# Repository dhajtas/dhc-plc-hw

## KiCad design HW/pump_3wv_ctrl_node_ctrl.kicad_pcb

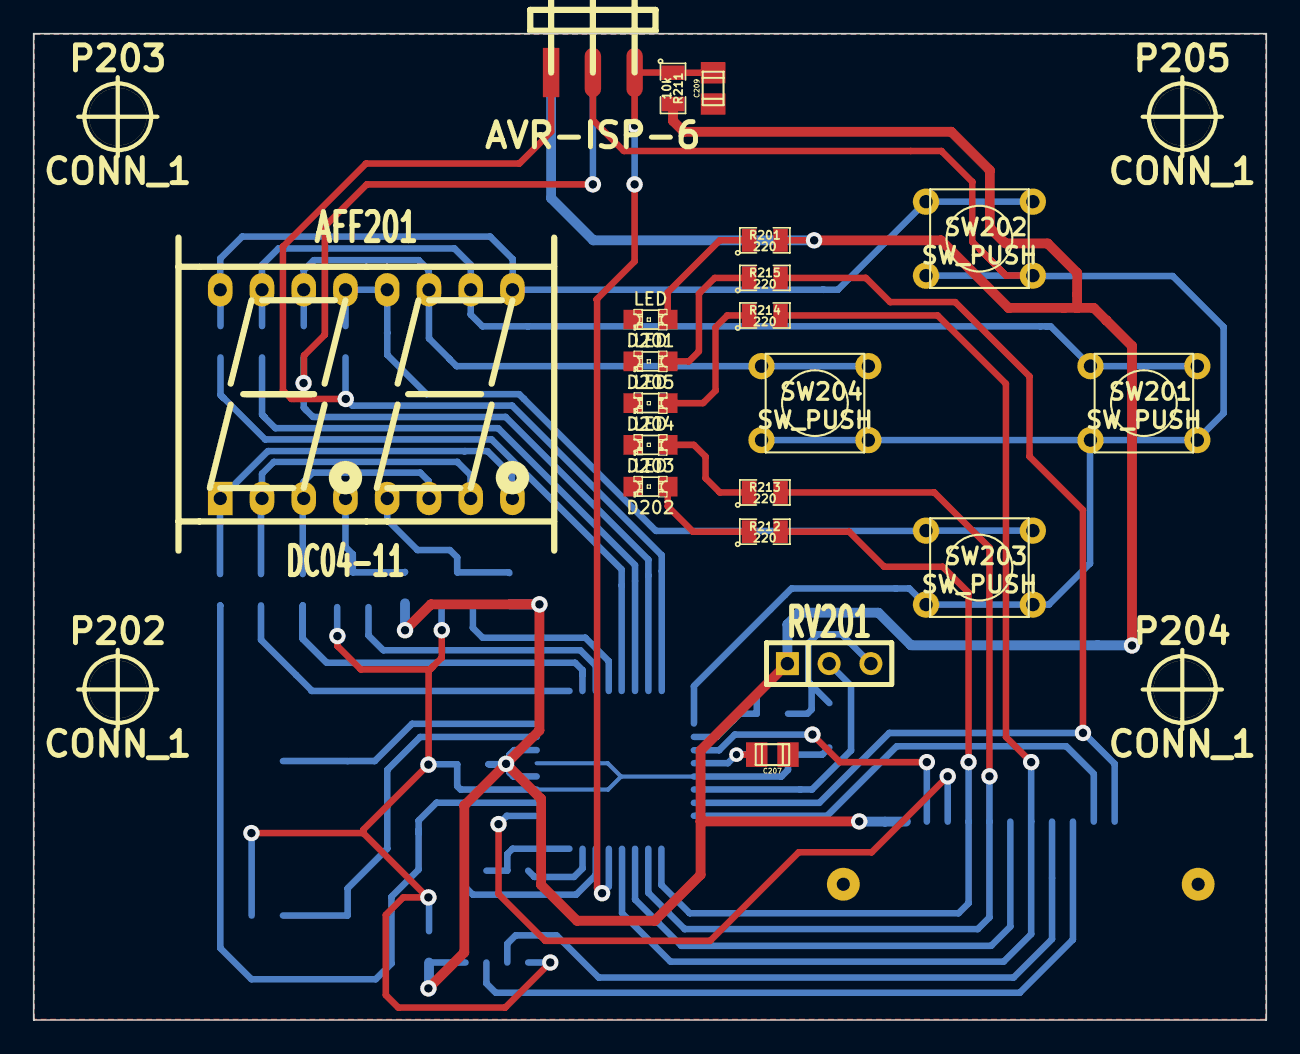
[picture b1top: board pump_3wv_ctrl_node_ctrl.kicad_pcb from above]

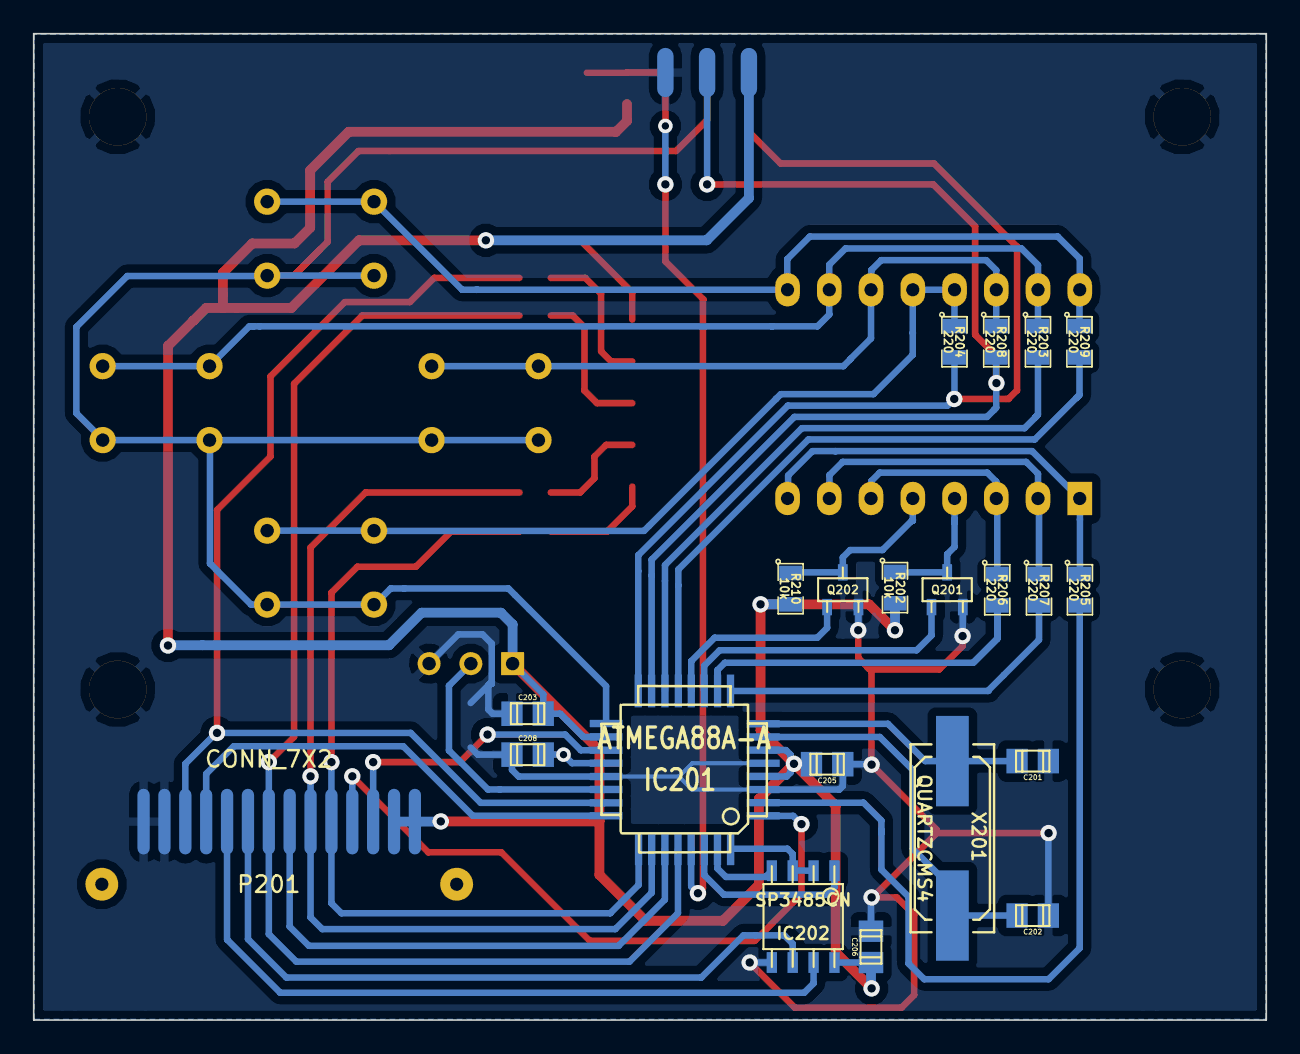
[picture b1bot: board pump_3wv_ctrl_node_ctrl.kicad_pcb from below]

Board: 2 copper layers, 75.0 x 60.0 mm, 45 parts (21 on the bottom side), 44 nets.

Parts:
AFF201: DC04-11; Dx04
C201, C202: 12p; c_0805
C203, C205, C206, C208: 100n; c_0805
C207, C209: 1u; c_0805
CON201: AVR-ISP-6; avr_isp_6_edge
D201, D202, D203, D204, D205: LED; LED-0805
IC201: ATMEGA88A-A; TQFP32
IC202: SP3485CN; so-8
P201: CONN_7X2; 14pin_flatcable_pcbstrip
P202, P203, P204, P205: CONN_1; hole_3mm5
Q201, Q202: MOS_N_DHA; sot23
R201, R203, R204, R205, R206, R207, R208, R209, R212, R213, R214, R215: 220; SM0805
R202, R210, R211: 10k; SM0805
RV201: POT; SIL-3
SW201, SW202, SW203, SW204: SW_PUSH; SW_KSM61x
X201: QUARTZCMS4; Q_49U3HMS

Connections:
+5V: C203.1, C205.1, C206.2, CON201.2, IC201.4, IC201.6, IC201.18, IC202.8, P201.1, P201.2, R201.2, R202.2, R210.2, R211.2, RV201.1
/485_A: IC202.6, P201.9
/485_B: IC202.7, P201.10
/A: AFF201.10, AFF201.15, R203.1, SW201.1
/AA: IC201.14, R203.2
/B: AFF201.12, AFF201.13, R204.1, SW203.1
/C: AFF201.1, AFF201.8, R205.1
/CC: IC201.2, R205.2
/D: AFF201.3, AFF201.6, R206.1
/D1: AFF201.4, Q201.2, R202.1
/D2: AFF201.5, Q202.2, R210.1
/DD: IC201.10, R206.2
/E: AFF201.2, AFF201.7, R207.1
/EE: IC201.9, R207.2
/F: AFF201.11, AFF201.14, R208.1, SW204.1
/G: AFF201.9, AFF201.16, R209.1, SW202.1
/G1: IC201.11, Q201.1
/G2: IC201.12, Q202.1
/GG: IC201.13, R209.2
/IN: IC201.19, P201.3
/MISO: CON201.1, IC201.16, R204.2
/MOSI: CON201.4, IC201.15, R208.2
/PULSE1: IC201.28, P201.8, R214.2
/PULSE2: IC201.26, P201.6, R213.2
/PULSE3: IC201.25, P201.5, R212.2
/SCK: CON201.3, IC201.17, SW201.2, SW202.2, SW203.2, SW204.2
/SWFB: IC201.24, P201.11
/SWITCH: IC201.23, P201.12, R215.2
/W1: IC201.27, P201.7
/ZCD: IC201.1, P201.4
/ref: C207.1, C208.1, IC201.20
/reset: C209.1, CON201.5, IC201.29, R211.1
/xtal1: C202.1, IC201.7, X201.2
/xtal2: C201.1, IC201.8, X201.1
GND: C201.2, C202.2, C203.2, C205.2, C206.1, C207.2, C208.2, C209.2, CON201.6, D201.2, D202.2, D203.2, D204.2, D205.2, IC201.3, IC201.5, IC201.21, IC202.5, P201.13, P201.14, P202.1, P203.1, P204.1, P205.1, Q201.3, Q202.3, RV201.3
unnamed: D205.1, R215.1
unnamed: D202.1, R212.1
unnamed: D203.1, R213.1
unnamed: D204.1, R214.1
unnamed: IC201.32, IC202.2, IC202.3
unnamed: IC201.30, IC202.1
unnamed: D201.1, R201.1
unnamed: IC201.22, RV201.2
unnamed: IC201.31, IC202.4

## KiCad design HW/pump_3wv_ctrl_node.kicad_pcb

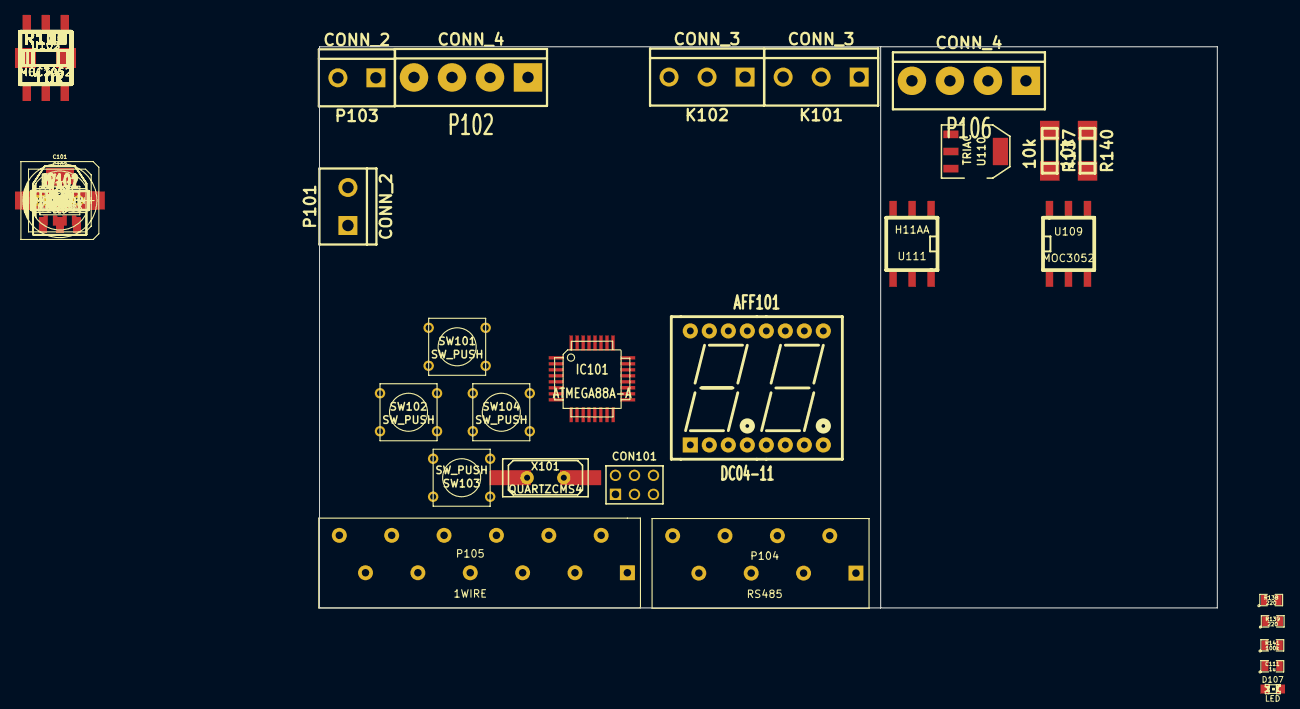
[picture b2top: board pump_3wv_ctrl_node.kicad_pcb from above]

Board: 2 copper layers, 120.0 x 75.0 mm, 94 parts (0 on the bottom side), 75 nets, no tracks yet.

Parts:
AFF101: DC04-11; Dx04
C101: 100u/63V; c_elec_10x10
C102: 470u/10V; c_elec_8x10
C103: 470p; SM0805
C104, C105: 12p; SM0805
C106, C107, C108, C110, C121: 100n; SM0805
C109: 1u; SM1206
C111: 1u; SM0805
C122: 10p; SM0805
CON101: AVR-ISP-6; pin_array_3x2
D101: transil 38V; SM2010
D102: SK110; SM0805
D103, D104, D105, D106, D107: LED; LED-0805
FB101: FILTER; SM0805
IC101: ATMEGA88A-A; TQFP32
JP101: JUMPER3; SIL-3
JP102: JUMPER; SIL-2
K101, K102: CONN_3; bornier3
P101, P103: CONN_2; bornier2
P102, P106: CONN_4; bornier4
P104: RS485; wago_250-208
P105: 1WIRE; wago_250-212
Q101, Q102: MOS_N_DHA; SOT23GDS
R101, R102, R104: 1; SM0805
R103: 100; SM0805
R105: 3k6; SM0805
R106: 1k2; SM0805
R107, R121, R133, R135, R136: 10k; SM0805
R108, R109, R110, R111, R113, R116, R117, R120, R122, R125, R137, R140: 10k; MELF0207
R112, R114, R115, R118, R119, R123, R124, R126, R127, R128, R129, R130, R131, R132, R138, R139: 220; SM0805
R134: 120; SM0805
R141: 100k; SM0805
RV101: POT; SIL-3
SW101, SW102, SW103, SW104: SW_PUSH; SW_PUSH_SMALL
U101: MC34063; SO8E
U102, U111: H11AA; SMD_DIL6
U103, U105, U107, U109: MOC3052; SMD_DIL6
U104, U106, U108, U110: TRIAC; SOT223
X101: QUARTZCMS4; Q_49_SMD_TH

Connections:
+5V: C102.1, C106.1, C107.1, C108.1, C121.2, CON101.2, IC101.4, IC101.6, IC101.18, JP101.1, P105.3, P105.6, P105.9, P105.12, R105.2, R107.1, R112.2, R121.2, R133.2, R135.2, R136.2, RV101.1
+24V: D101.2, JP101.3, P101.1, R103.1
/A: AFF101.10, AFF101.15, JP102.2, P104.3, P104.7, R126.1, SW101.1
/B: AFF101.12, AFF101.13, P104.2, P104.6, R127.1, R134.1, SW102.1
/C: AFF101.1, AFF101.8, R128.1, SW103.1
/D: AFF101.3, AFF101.6, R129.1, SW104.1
/D1: AFF101.4, R135.1
/D2: AFF101.5, R136.1
/E: AFF101.2, AFF101.7, R130.1
/F: AFF101.11, AFF101.14, R131.1
/G: AFF101.9, AFF101.16, R132.1
/G3: IC101.26, SW101.2, SW102.2, SW103.2, SW104.2
/IN: IC101.19, P103.1, R133.1
/L: K101.3, P106.2, R111.1, R113.1, R117.1, R122.1, U104.2, U106.2, U108.2
/L1: K102.3, U108.1
/L2: P102.4, U106.1
/L3: P102.3, U104.1
/N: K101.1, K102.1, P102.1, P106.1, R109.1, U111.1
/PULSE1: IC101.2, R123.2, R124.2
/PULSE2: IC101.9, R118.2, R119.2
/PULSE3: IC101.10, R114.2, R115.2
/PWR1: FB101.1, R103.2
/PWR2: C101.1, FB101.2, R101.1, R102.1, R104.1, U101.6
/PWR3: R101.2, R102.2, R104.2, U101.1, U101.7, U101.8
/PWR4: D102.2, U101.2
/SWFB: C111.1, IC101.27, R141.2, U111.5
/SWITCH: IC101.28, R138.2, R139.2
/W1: IC101.11, P105.2, P105.5, P105.8, P105.11
/ZCD: IC101.1, R107.2, U102.5
/ref: C109.1, C110.1, IC101.20
/reset: C122.1, CON101.5, IC101.29, R121.1
/xtal1: C105.1, IC101.7
/xtal2: C104.1, IC101.8, X101.1
GND: C101.2, C102.2, C103.2, C104.2, C105.2, C106.2, C107.2, C108.2, C109.2, C110.2, C111.2, C121.1, C122.2, CON101.6, D101.1, D102.1, D103.2, D104.2, D105.2, D106.2, D107.2, IC101.3, IC101.5, IC101.21, P101.2, P103.2, P104.1, P104.5, P105.1, P105.4, P105.7, P105.10, R106.1, RV101.3, U101.4, U102.4, U103.2, U105.2, U107.2, U109.2, U111.4
unnamed: D103.1, R112.1
unnamed: JP102.1, R134.2
unnamed: D106.1, R124.1
unnamed: D105.1, R119.1
unnamed: D104.1, R115.1
unnamed: IC101.22, RV101.2
unnamed: R116.2, U103.4
unnamed: R116.1, U104.3
unnamed: R120.1, U106.3
unnamed: R120.2, U105.4
unnamed: R125.2, U107.4
unnamed: R125.1, U108.3
unnamed: R113.2, U103.6
unnamed: R108.1, R109.2
unnamed: R108.2, U102.1
unnamed: R110.2, U102.2
unnamed: R110.1, R111.2
unnamed: K101.2, K102.2, P102.2
unnamed: R118.1, U105.1
unnamed: R123.1, U107.1
unnamed: R117.2, U105.6
unnamed: R122.2, U107.6
unnamed: IC101.23, R132.2
unnamed: R114.1, U103.1
unnamed: P106.3, U110.1
unnamed: R140.1, U110.3
unnamed: R140.2, U109.4
unnamed: R137.1, U110.2
unnamed: P106.4, U111.2
unnamed: R137.2, U109.6
unnamed: R138.1, U109.1
unnamed: D107.1, R139.1
unnamed: IC101.13, R130.2
unnamed: IC101.12, R126.2
unnamed: CON101.4, IC101.15, R127.2
unnamed: CON101.3, IC101.17, R129.2
unnamed: IC101.14, R131.2
unnamed: CON101.1, IC101.16, R128.2
unnamed: R105.1, R106.2, U101.5
unnamed: C103.1, U101.3
unnamed: JP101.2, P104.4, P104.8

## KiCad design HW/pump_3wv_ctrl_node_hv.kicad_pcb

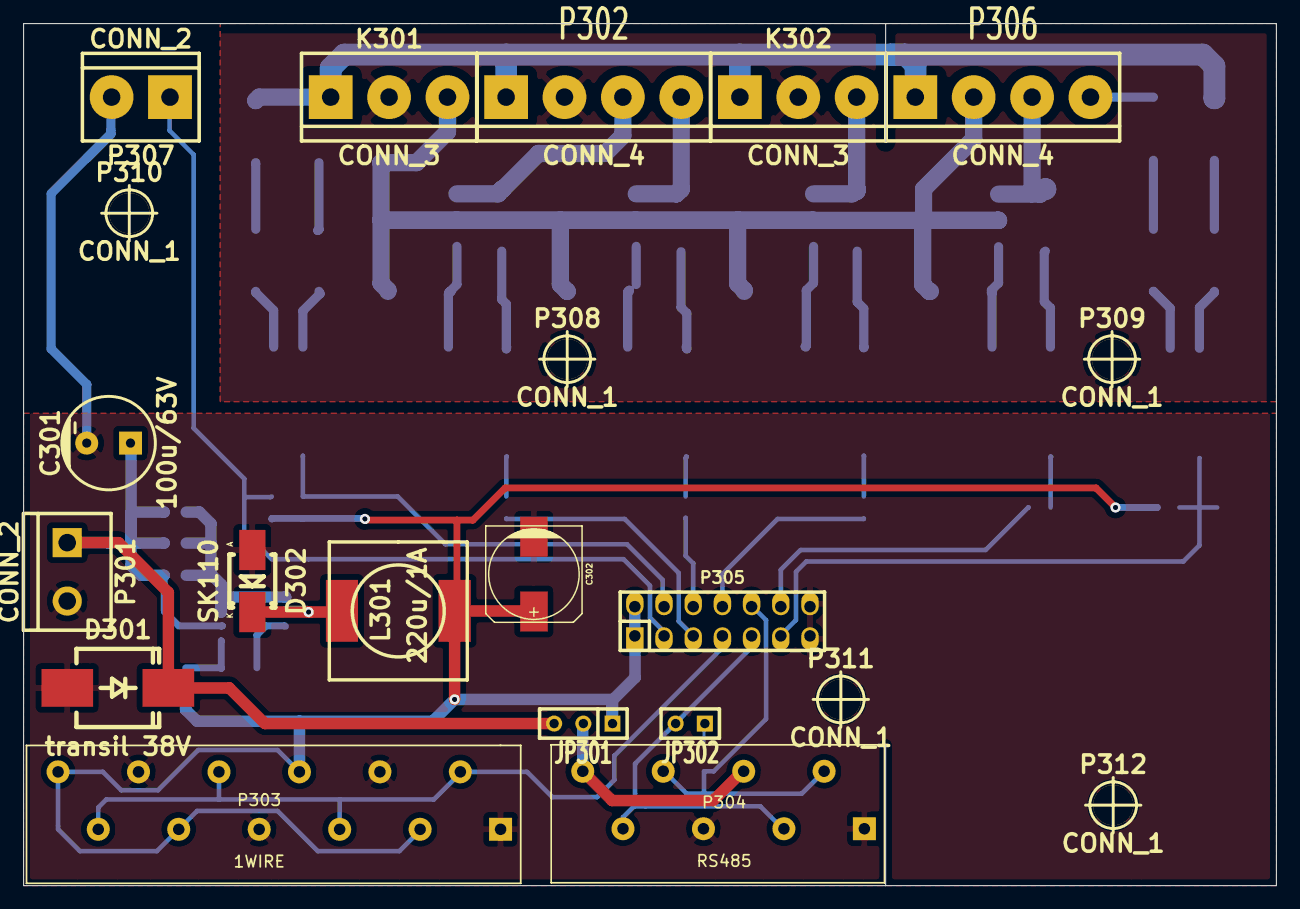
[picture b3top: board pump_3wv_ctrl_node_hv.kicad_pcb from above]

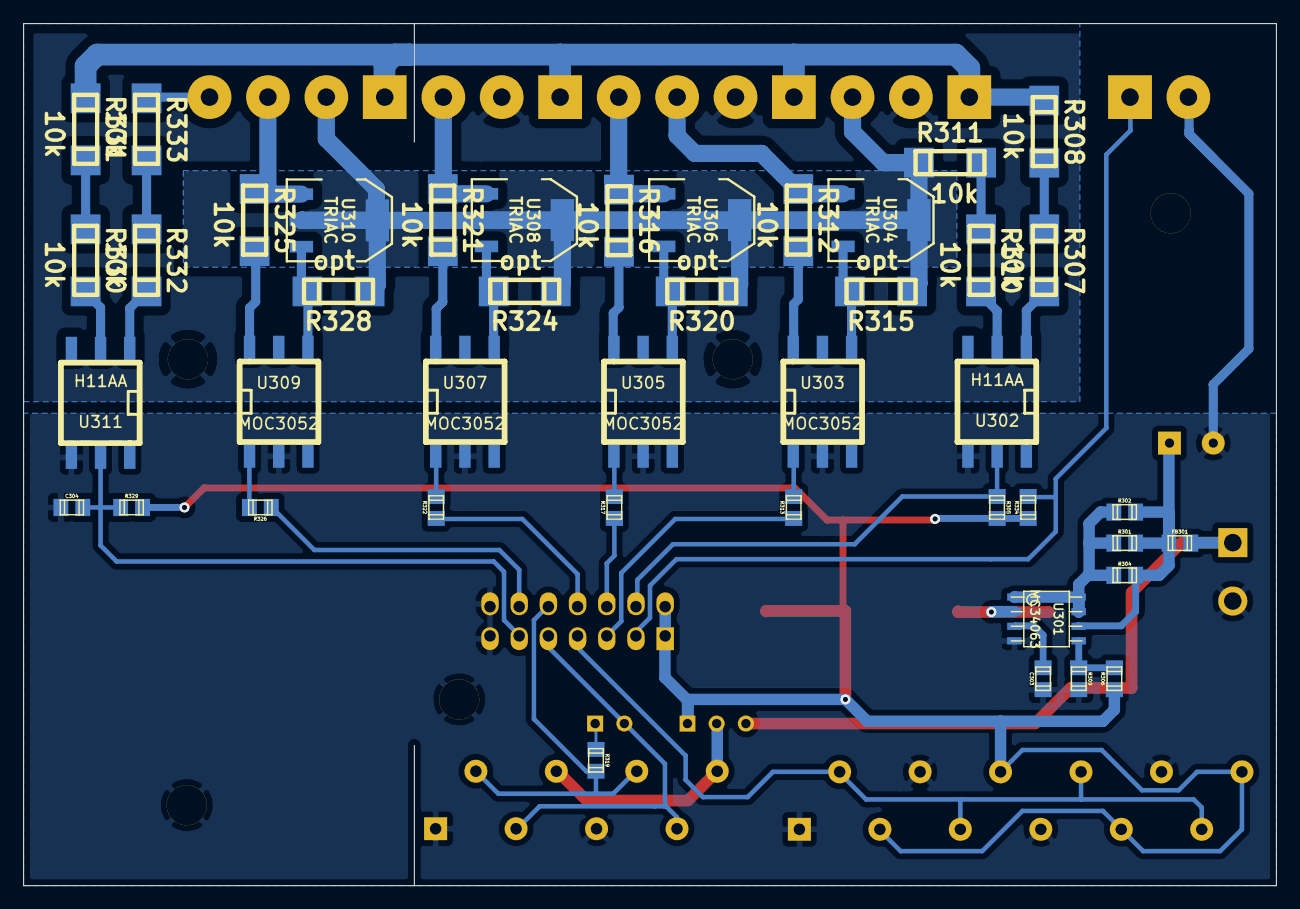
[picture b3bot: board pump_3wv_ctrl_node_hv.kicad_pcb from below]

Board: 2 copper layers, 109.0 x 75.0 mm, 64 parts (43 on the bottom side), 48 nets.

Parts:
C301: 100u/63V; CP_8x13mm
C302: 470u/10V; c_elec_8x10
C303: 470p; c_0805
C304: 1u; c_0805
D301: transil 38V; Diode-SMC_Handsoldering_RevA_27July2010
D302: SK110; Diode-SMB_Handsoldering_RevA_27July2010
FB301: FILTER; r_0805
JP301: JUMPER3; SIL-3
JP302: JUMPER; SIL-2
K301, K302: CONN_3; bornier3
L301: 220u/1A; L_SMD_12x12
P301, P307: CONN_2; bornier2
P302, P306: CONN_4; bornier4
P303: 1WIRE; wago_250-212
P304: RS485; wago_250-208
P305: CONN_7X2; pin_strip_7x2
P308, P309, P310, P311, P312: CONN_1; hole_3mm5
R301, R302, R304: 1; r_0805
R305, R334: 10k; r_0805
R306: 3k6; r_0805
R307, R308, R310, R311, R312, R316, R321, R325, R330, R331, R332, R333: 10k; MELF0207
R309: 1k2; r_0805
R313, R317, R322, R326: 220; r_0805
R315, R320, R324, R328: opt; MELF0207
R319: 120; r_0805
R329: 100k; r_0805
U301: MC34063; so-8
U302, U311: H11AA; SMD_DIL6
U303, U305, U307, U309: MOC3052; SMD_DIL6
U304, U306, U308, U310: TRIAC; SOT223_3pin

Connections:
+5V: C302.1, JP301.1, L301.2, P303.3, P303.6, P303.9, P303.12, P305.1, P305.2, R305.1, R306.2, R329.1, R334.2
+24V: D301.2, FB301.1, JP301.3, P301.1
/A: JP302.2, P304.3, P304.7, P305.9
/B: P304.2, P304.6, P305.10, R319.1
/HV_PG1: R324.2, U307.4, U308.3
/HV_PG2: R320.2, U305.4, U306.3
/HV_PG3: R315.2, U303.4, U304.3
/HV_PG4: R328.2, U309.4, U310.3
/HV_PN1: R321.2, U307.6
/HV_PN2: R316.2, U305.6
/HV_PN3: R312.2, U303.6
/HV_PN4: R325.2, U309.6
/IN: P305.3, P307.1, R334.1
/L: K301.3, P306.2, R311.1, R315.1, R320.1, R324.1, R328.1, U304.2, U306.2, U308.2, U310.2
/L1: K302.3, R321.1, U308.1
/L2: P302.4, R316.1, U306.1
/L3: P302.3, R312.1, U304.1
/L4: P306.3, R325.1, U310.1
/LL1: R310.2, U302.2
/LL2: R332.2, U311.1
/N: K301.1, K302.1, P302.1, P306.1, R308.1, R331.1
/NN1: R307.2, U302.1
/NN2: R330.2, U311.2
/P1: R322.1, U307.1
/P2: R317.1, U305.1
/P3: R313.1, U303.1
/P4: R326.1, U309.1
/PE: K301.2, K302.2, P302.2, P308.1, P309.1
/PULSE1: P305.8, R322.2
/PULSE2: P305.6, R317.2
/PULSE3: P305.5, R313.2
/PWR2: C301.1, FB301.2, R301.1, R302.1, R304.1, U301.6
/PWR3: R301.2, R302.2, R304.2, U301.1, U301.7, U301.8
/PWR4: D302.2, L301.1, U301.2
/SWFB: C304.1, P305.11, R329.2, U311.5
/SWITCH: P305.12, R326.2
/W1: P303.2, P303.5, P303.8, P303.11, P305.7
/ZCD: P305.4, R305.2, U302.5
/lll1: R310.1, R311.2
/lll2: R332.1, R333.2
/llll2: P306.4, R333.1
/nnn1: R307.1, R308.2
/nnn2: R330.1, R331.2
GND: C301.2, C302.2, C303.2, C304.2, D301.1, D302.1, P301.2, P303.1, P303.4, P303.7, P303.10, P304.1, P304.5, P305.13, P305.14, P307.2, P311.1, P312.1, R309.1, U301.4, U302.4, U303.2, U305.2, U307.2, U309.2, U311.4
unnamed: JP302.1, R319.2
unnamed: JP301.2, P304.4, P304.8
unnamed: C303.1, U301.3
unnamed: R306.1, R309.2, U301.5

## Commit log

2014-01-14 pin definitions
2014-01-23 Added onewire files
2015-04-16 Migrating wiki contents from Google Code
